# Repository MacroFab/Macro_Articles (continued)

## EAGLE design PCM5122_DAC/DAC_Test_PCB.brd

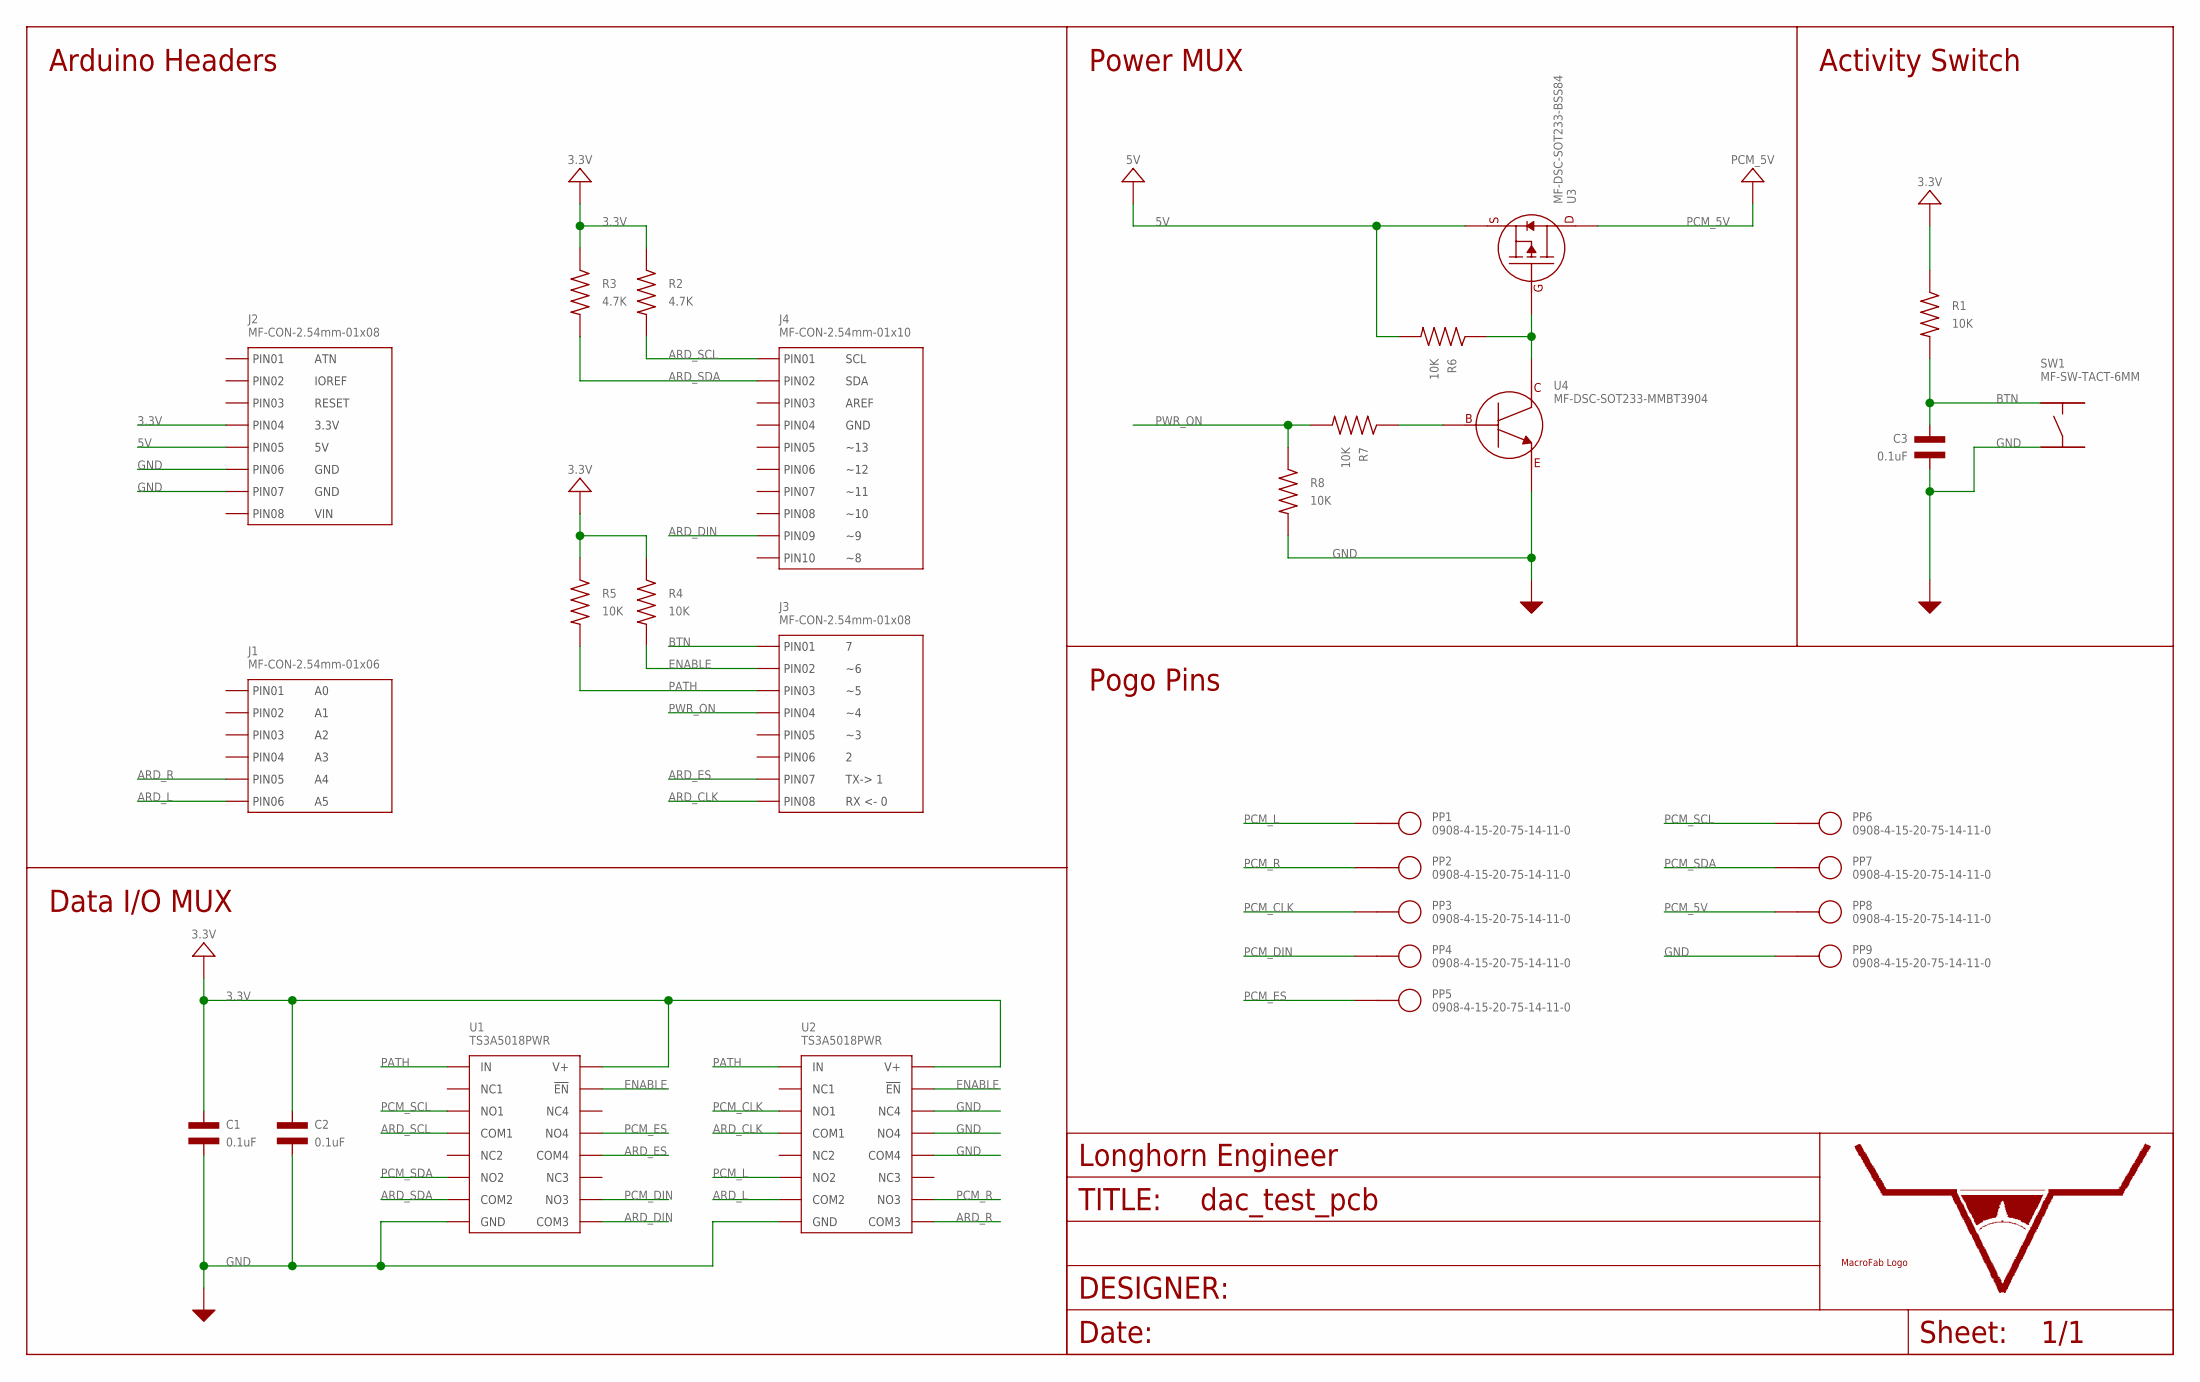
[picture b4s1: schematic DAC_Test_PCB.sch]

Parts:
C1, C2, C3: 0.1uF; C0603
J1: MF-CON-2.54mm-01x06; PTH_2.54MM_01X06
J2, J3: MF-CON-2.54mm-01x08; PTH_2.54MM_01X08
J4: MF-CON-2.54mm-01x10; PTH_2.54MM_01X10
PP1, PP2, PP3, PP4, PP5, PP6, PP7, PP8, PP9: 0908-4-15-20-75-14-11-0
R1, R4, R5, R6, R7, R8: 10K; R0603
R2, R3: 4.7K; R0603
SW1: MF-SW-TACT-6MM; TACT6MM
U1, U2: TS3A5018PWR; TS3A5018_TTSOP-16
U3: MF-DSC-SOT233-BSS84; SOT-23-3
U4: MF-DSC-SOT233-MMBT3904; SOT-23-3
U$8: LHE_FRAME
U$9: MF_LOGOLOGO_MEDIUM; MF_LOGO_MEDIUM

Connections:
3.3V: C1.P$1, C2.P$1, J2.P$4 (PIN4), R1.P$1, R2.P$1, R3.P$1, R4.P$1, R5.P$1, U1.16 (V+), U2.16 (V+)
5V: J2.P$5 (PIN5), R6.P$2, U3.P$2 (SOURCE)
ARD_CLK: J3.P$8 (PIN8), U2.4 (COM1)
ARD_DIN: J4.P$9 (PIN9), U1.9 (COM3)
ARD_ES: J3.P$7 (PIN7), U1.12 (COM4)
ARD_L: J1.P$6 (PIN6), U2.7 (COM2)
ARD_R: J1.P$5 (PIN5), U2.9 (COM3)
ARD_SCL: J4.P$1 (PIN1), R2.P$2, U1.4 (COM1)
ARD_SDA: J4.P$2 (PIN2), R3.P$2, U1.7 (COM2)
BASE: R7.P$1, U4.P$1 (BASE)
BTN: C3.P$1, J3.P$1 (PIN1), R1.P$2, SW1.P$1
COLLECTOR: R6.P$1, U3.P$1 (GATE), U4.P$3 (COLLECTOR)
ENABLE: J3.P$2 (PIN2), R4.P$2, U1.15 (EN'), U2.15 (EN')
GND: C1.P$2, C2.P$2, C3.P$2, J2.P$6 (PIN6), J2.P$7 (PIN7), PP9.P$1, R8.P$2, SW1.P$3, U1.8 (GND), U2.8 (GND), U2.12 (COM4), U2.13 (NO4), U2.14 (NC4), U4.P$2 (EMITTER)
PATH: J3.P$3 (PIN3), R5.P$2, U1.1 (IN), U2.1 (IN)
PCM_5V: PP8.P$1, U3.P$3 (DRAIN)
PCM_CLK: PP3.P$1, U2.3 (NO1)
PCM_DIN: PP4.P$1, U1.10 (NO3)
PCM_ES: PP5.P$1, U1.13 (NO4)
PCM_L: PP1.P$1, U2.6 (NO2)
PCM_R: PP2.P$1, U2.10 (NO3)
PCM_SCL: PP6.P$1, U1.3 (NO1)
PCM_SDA: PP7.P$1, U1.6 (NO2)
PWR_ON: J3.P$4 (PIN4), R7.P$2, R8.P$1

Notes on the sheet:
Arduino Headers
Data I/O MUX
Power MUX
Activity Switch
Pogo Pins

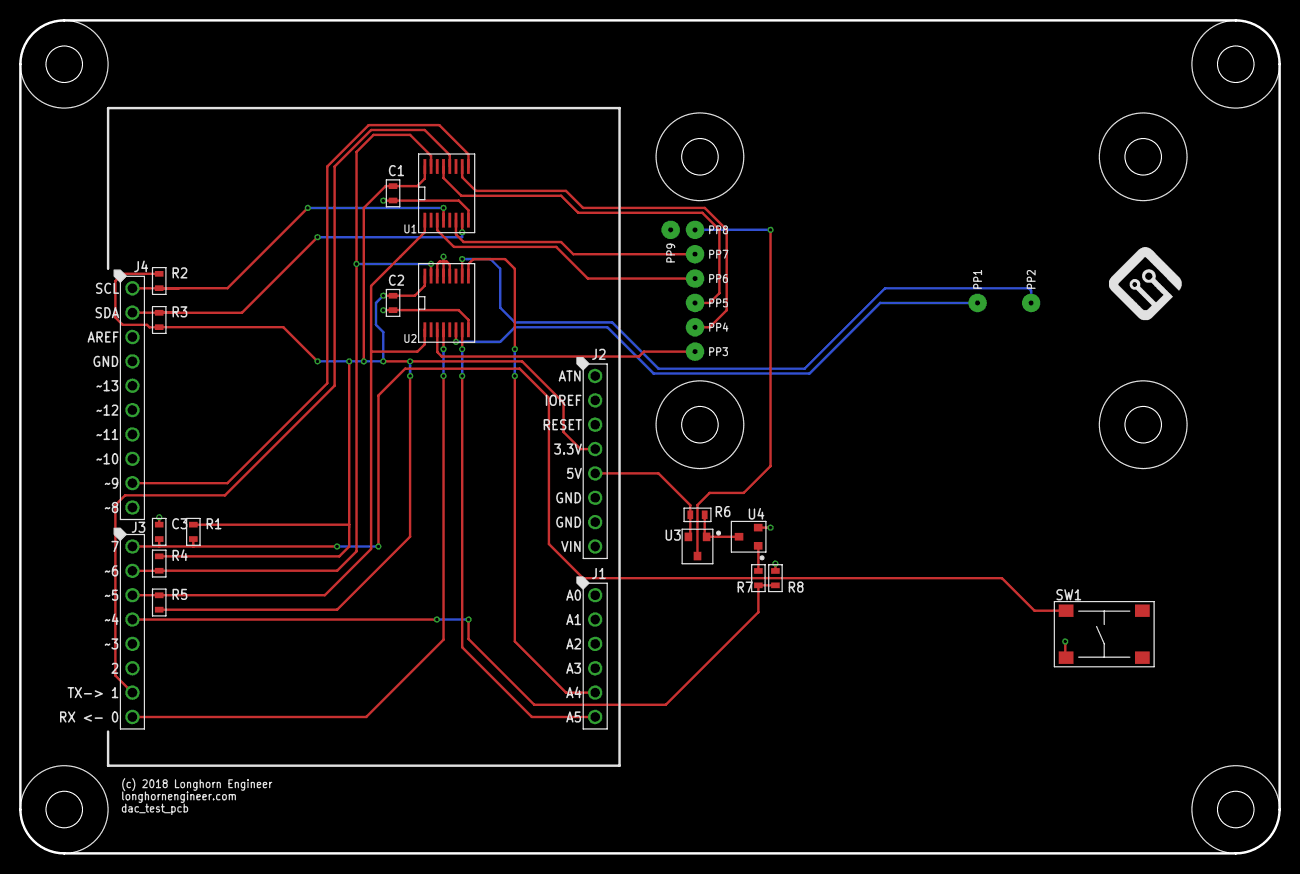
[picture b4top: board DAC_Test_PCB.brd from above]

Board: 2 copper layers, 131.3 x 86.9 mm, 39 parts (0 on the bottom side), 24 nets.

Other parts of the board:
U$4, U$5, U$6, U$7, U$16, U$17, U$18, U$19: MOUNT_HOLE_150MIL

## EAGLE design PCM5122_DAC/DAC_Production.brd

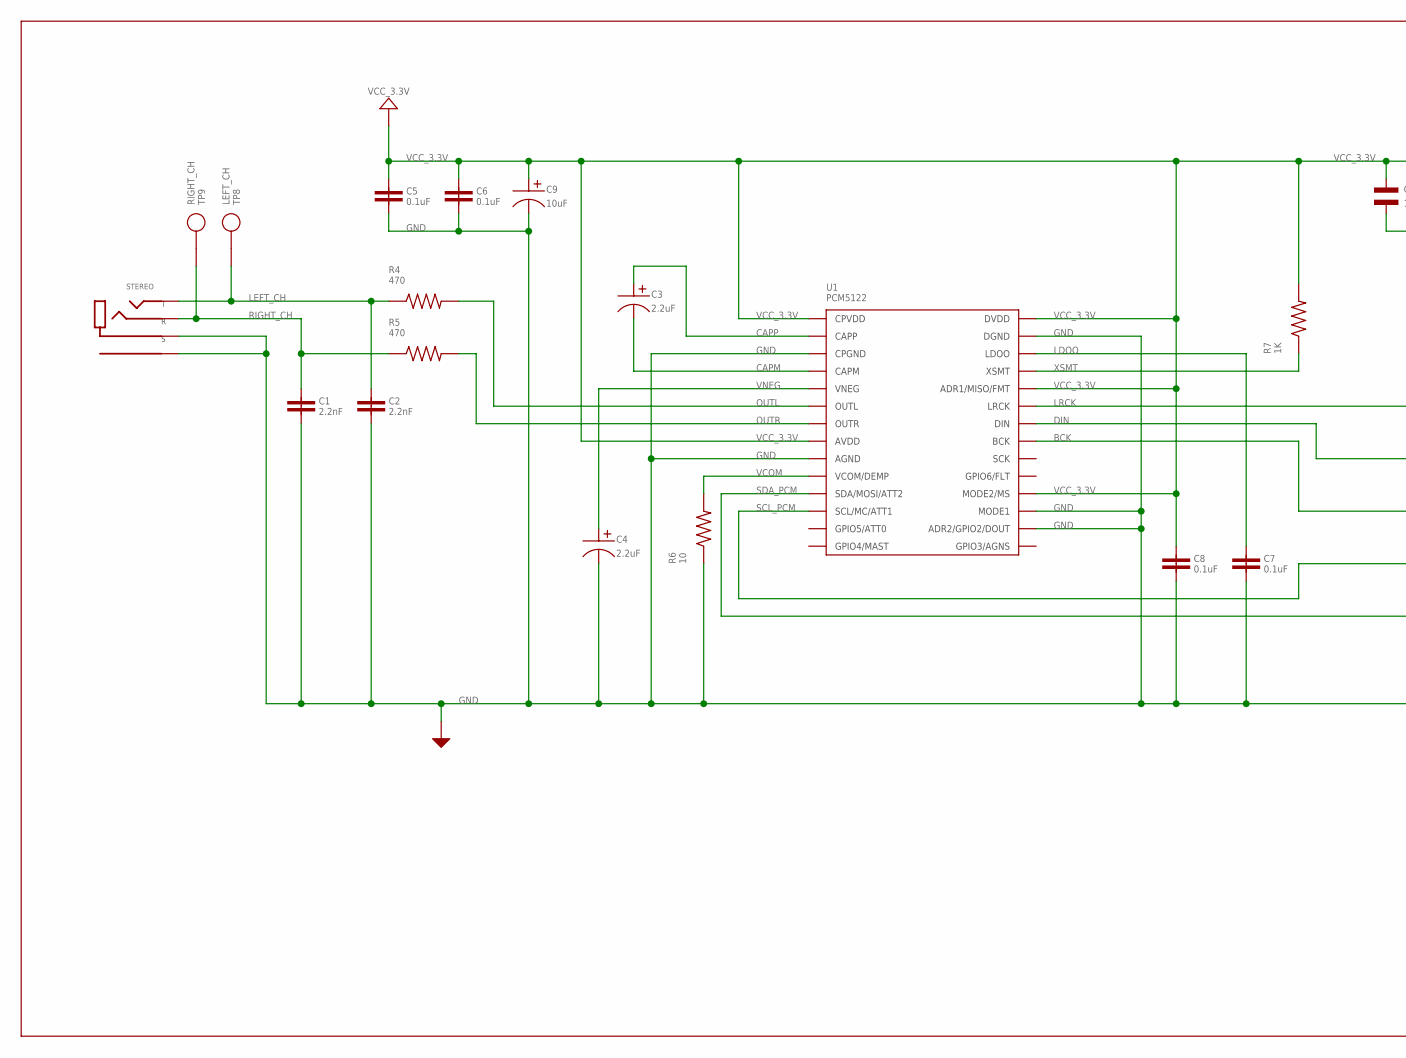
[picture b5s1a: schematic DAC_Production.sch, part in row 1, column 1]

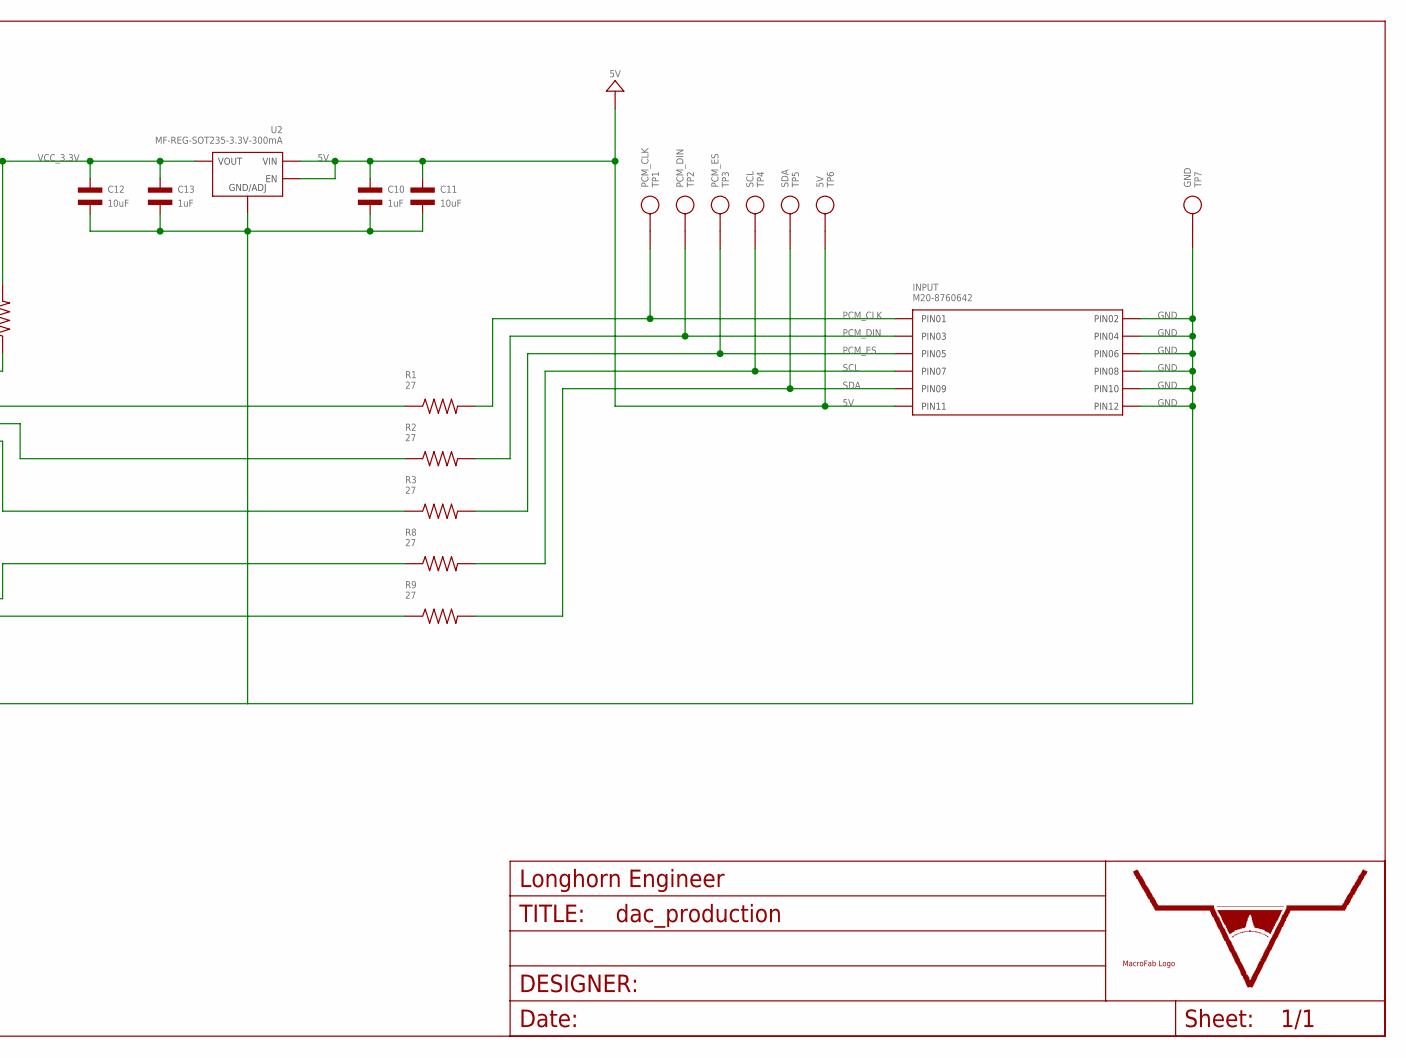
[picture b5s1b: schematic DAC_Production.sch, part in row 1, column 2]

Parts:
C1, C2: 2.2nF; 0805; MPN VJ0805A222KXXPW1BC
C3, C4: 2.2uF; CP4MM; MPN UUQ1H2R2MCL1GB
C5, C6, C7, C8: 0.1uF; 0805; MPN 885012207072
C9: 10uF; CP4MM; MPN UUQ1A100MCL1GB
C10, C13: 1uF; C0805; MPN MF-CAP-0805-1uF
C11, C12: 10uF; C1206; MPN MF-CAP-1206-10uF
INPUT: M20-8760642
R1, R2, R3, R8, R9: 27; 0603; MPN MF-RES-0603-27
R4, R5: 470; 0603; MPN MF-RES-0603-470
R6: 10; 0603; MPN MF-RES-0603-10
R7: 1K; 0603; MPN MF-RES-0603-1K
STEREO: TRS_SHIELD_JACK_SJ1-3533NS; SJ1-3533NS
TP1: PCM_CLK; ROUND_TP
TP2: PCM_DIN; ROUND_TP
TP3: PCM_ES; ROUND_TP
TP4: SCL; ROUND_TP
TP5: SDA; ROUND_TP
TP6: 5V; ROUND_TP
TP7: GND; ROUND_TP
TP8: LEFT_CH; ROUND_TP
TP9: RIGHT_CH; ROUND_TP
U1: PCM5122; PCM5122_TTSOP-28
U2: MF-REG-SOT235-3.3V-300mA; SOT-23-5
U$8: LHE_FRAME
U$9: MF_LOGOLOGO_MEDIUM; MF_LOGO_MEDIUM

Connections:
5V: C10.P$1, C11.P$1, INPUT.P$11 (PIN11), TP6.P$1, U2.P$1 (VIN), U2.P$3 (EN)
BCK: R3.1, U1.P$21 (BCK)
CAPM: C3.P$2, U1.P$4 (CAPM)
CAPP: C3.P$1, U1.P$2 (CAPP)
DIN: R2.1, U1.P$22 (DIN)
GND: C1.2, C2.2, C4.P$2, C5.2, C6.2, C7.2, C8.2, C9.P$2, C10.P$2, C11.P$2, C12.P$2, C13.P$2, INPUT.P$2 (PIN2), INPUT.P$4 (PIN4), INPUT.P$6 (PIN6), INPUT.P$8 (PIN8), INPUT.P$10 (PIN10), INPUT.P$12 (PIN12), R6.1, STEREO.1_A (S), STEREO.1_B (S), STEREO.S1 (SHIELD), STEREO.S2 (SHIELD), STEREO.S3 (SHIELD), STEREO.S4 (SHIELD), STEREO.S5 (SHIELD), STEREO.S6 (SHIELD), TP7.P$1, U1.P$3 (CPGND), U1.P$9 (AGND), U1.P$16 (ADR2/GPIO2/DOUT), U1.P$17 (MODE1), U1.P$27 (DGND), U2.P$2 (GND/ADJ)
LDOO: C7.1, U1.P$26 (LDOO)
LEFT_CH: C2.1, R4.1, STEREO.2_A (T), STEREO.2_B (T), TP8.P$1
LRCK: R1.1, U1.P$23 (LRCK)
OUTL: R4.2, U1.P$6 (OUTL)
OUTR: R5.2, U1.P$7 (OUTR)
PCM_CLK: INPUT.P$1 (PIN1), R1.2, TP1.P$1
PCM_DIN: INPUT.P$3 (PIN3), R2.2, TP2.P$1
PCM_ES: INPUT.P$5 (PIN5), R3.2, TP3.P$1
RIGHT_CH: C1.1, R5.1, STEREO.3_A (R), STEREO.3_B (R), TP9.P$1
SCL: INPUT.P$7 (PIN7), R8.2, TP4.P$1
SCL_PCM: R8.1, U1.P$12 (SCL/MC/ATT1)
SDA: INPUT.P$9 (PIN9), R9.2, TP5.P$1
SDA_PCM: R9.1, U1.P$11 (SDA/MOSI/ATT2)
VCC_3.3V: C5.1, C6.1, C8.1, C9.P$1, C12.P$1, C13.P$1, R7.2, U1.P$1 (CPVDD), U1.P$8 (AVDD), U1.P$18 (MODE2/MS), U1.P$24 (ADR1/MISO/FMT), U1.P$28 (DVDD), U2.P$5 (VOUT)
VCOM: R6.2, U1.P$10 (VCOM/DEMP)
VNEG: C4.P$1, U1.P$5 (VNEG)
XSMT: R7.1, U1.P$25 (XSMT)

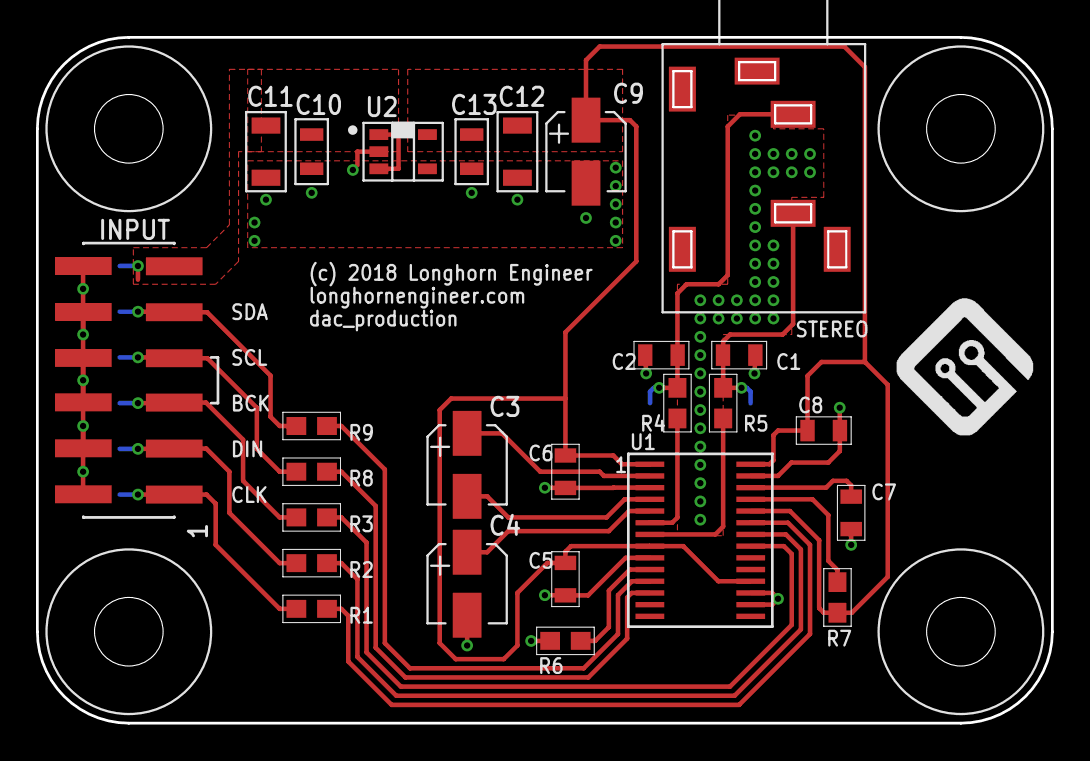
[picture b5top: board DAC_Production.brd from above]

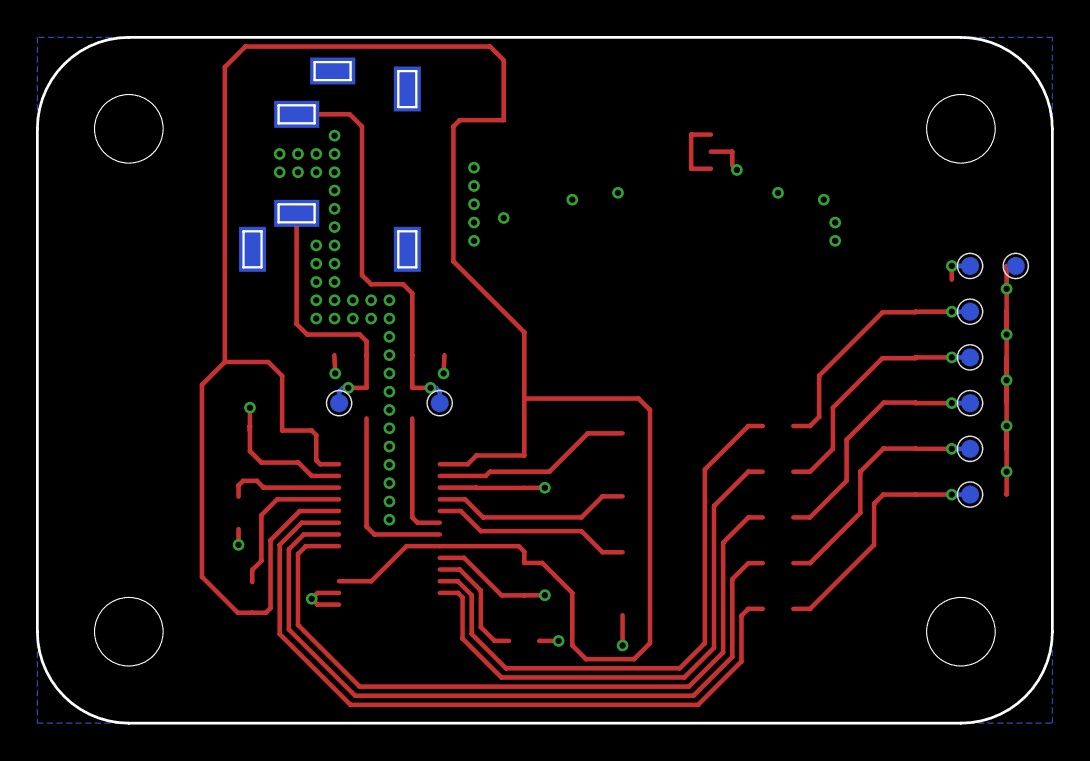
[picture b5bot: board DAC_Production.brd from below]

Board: 2 copper layers, 56.4 x 38.1 mm, 41 parts (9 on the bottom side), 23 nets.

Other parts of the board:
U$4, U$5, U$6, U$7: MOUNT_HOLE_150MIL

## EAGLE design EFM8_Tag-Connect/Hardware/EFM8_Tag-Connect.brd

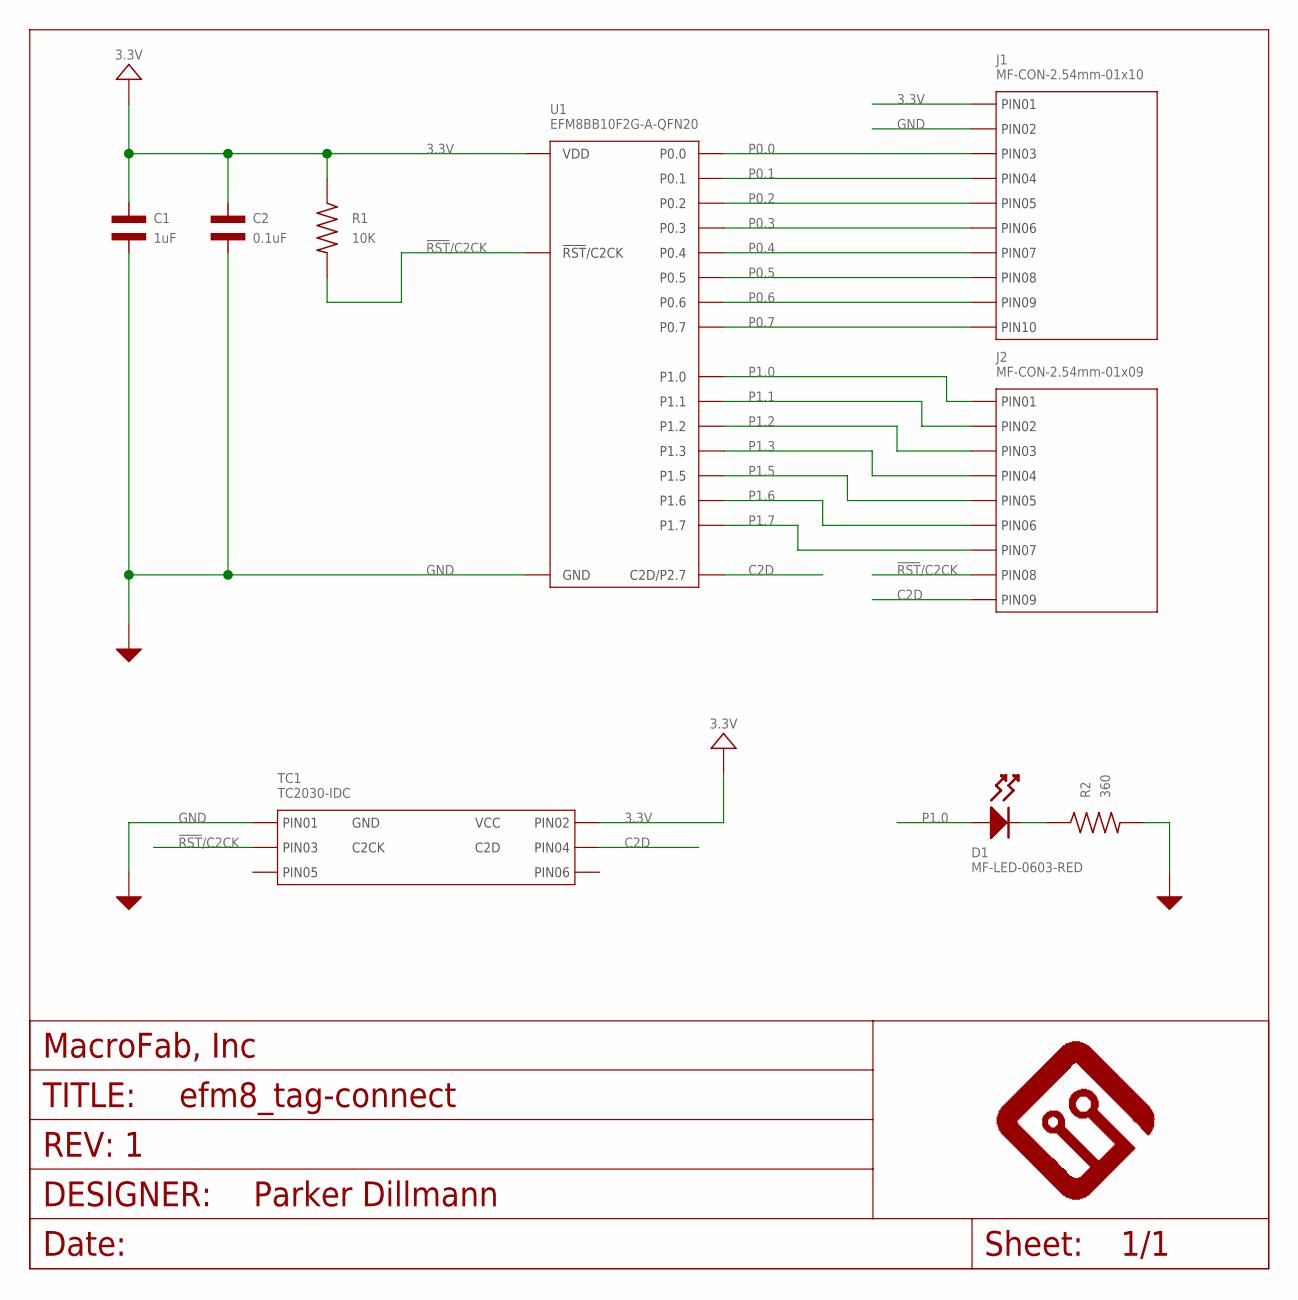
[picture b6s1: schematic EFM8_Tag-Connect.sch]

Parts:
C1: 1uF; C0402; MPN MF-CAP-0402-1uF
C2: 0.1uF; C0402; MPN MF-CAP-0402-0.1uF
D1: MF-LED-0603-RED; LED0603
FRAME1: MF_FRAMEDEFAULT; MF_FRAME_DEFAULT
J1: MF-CON-2.54mm-01x10; PTH_2.54MM_01X10
J2: MF-CON-2.54mm-01x09; PTH_2.54MM_01X09
R1: 10K; R0402; MPN MF-RES-0402-10K
R2: 360; R0402; MPN MF-RES-0402-360
TC1: TC2030-IDC; TC2030-IDC-FP
U1: EFM8BB10F2G-A-QFN20; EFM8BB10F(2/4/8)G-A-QFN20; MPN EFM8BB10F2G-A-QFN20

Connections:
3.3V: C1.P$1, C2.P$1, J1.P$1 (PIN1), R1.P$1, TC1.P$2 (PIN2), U1.P$4 (VDD)
!RST!/C2CK: J2.P$8 (PIN8), R1.P$2, TC1.P$3 (PIN3), U1.P$5 (!RST!/C2CK)
C2D: J2.P$9 (PIN9), TC1.P$4 (PIN4), U1.P$6 (C2D/P2.7)
GND: C1.P$2, C2.P$2, J1.P$2 (PIN2), R2.P$2, TC1.P$1 (PIN1), U1.P$3 (GND), U1.P$12 (GND), U1.PAD (GND)
unnamed: D1.CATHODE, R2.P$1
P0.0: J1.P$3 (PIN3), U1.P$2 (P0.0)
P0.1: J1.P$4 (PIN4), U1.P$1 (P0.1)
P0.2: J1.P$5 (PIN5), U1.P$20 (P0.2)
P0.3: J1.P$6 (PIN6), U1.P$19 (P0.3)
P0.4: J1.P$7 (PIN7), U1.P$18 (P0.4)
P0.5: J1.P$8 (PIN8), U1.P$17 (P0.5)
P0.6: J1.P$9 (PIN9), U1.P$16 (P0.6)
P0.7: J1.P$10 (PIN10), U1.P$15 (P0.7)
P1.0: D1.ANODE, J2.P$1 (PIN1), U1.P$14 (P1.0)
P1.1: J2.P$2 (PIN2), U1.P$13 (P1.1)
P1.2: J2.P$3 (PIN3), U1.P$11 (P1.2)
P1.3: J2.P$4 (PIN4), U1.P$10 (P1.3)
P1.5: J2.P$5 (PIN5), U1.P$8 (P1.5)
P1.6: J2.P$6 (PIN6), U1.P$7 (P1.6)
P1.7: J2.P$7 (PIN7), U1.P$9 (P1.7)

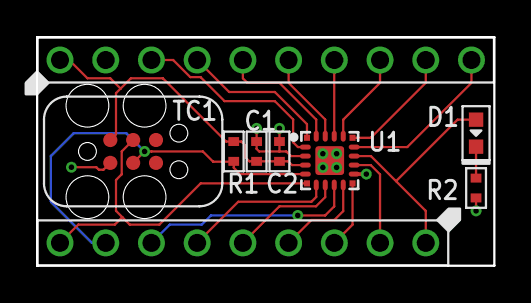
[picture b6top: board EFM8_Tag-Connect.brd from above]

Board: 2 copper layers, 25.4 x 12.7 mm, 10 parts (1 on the bottom side), 20 nets.

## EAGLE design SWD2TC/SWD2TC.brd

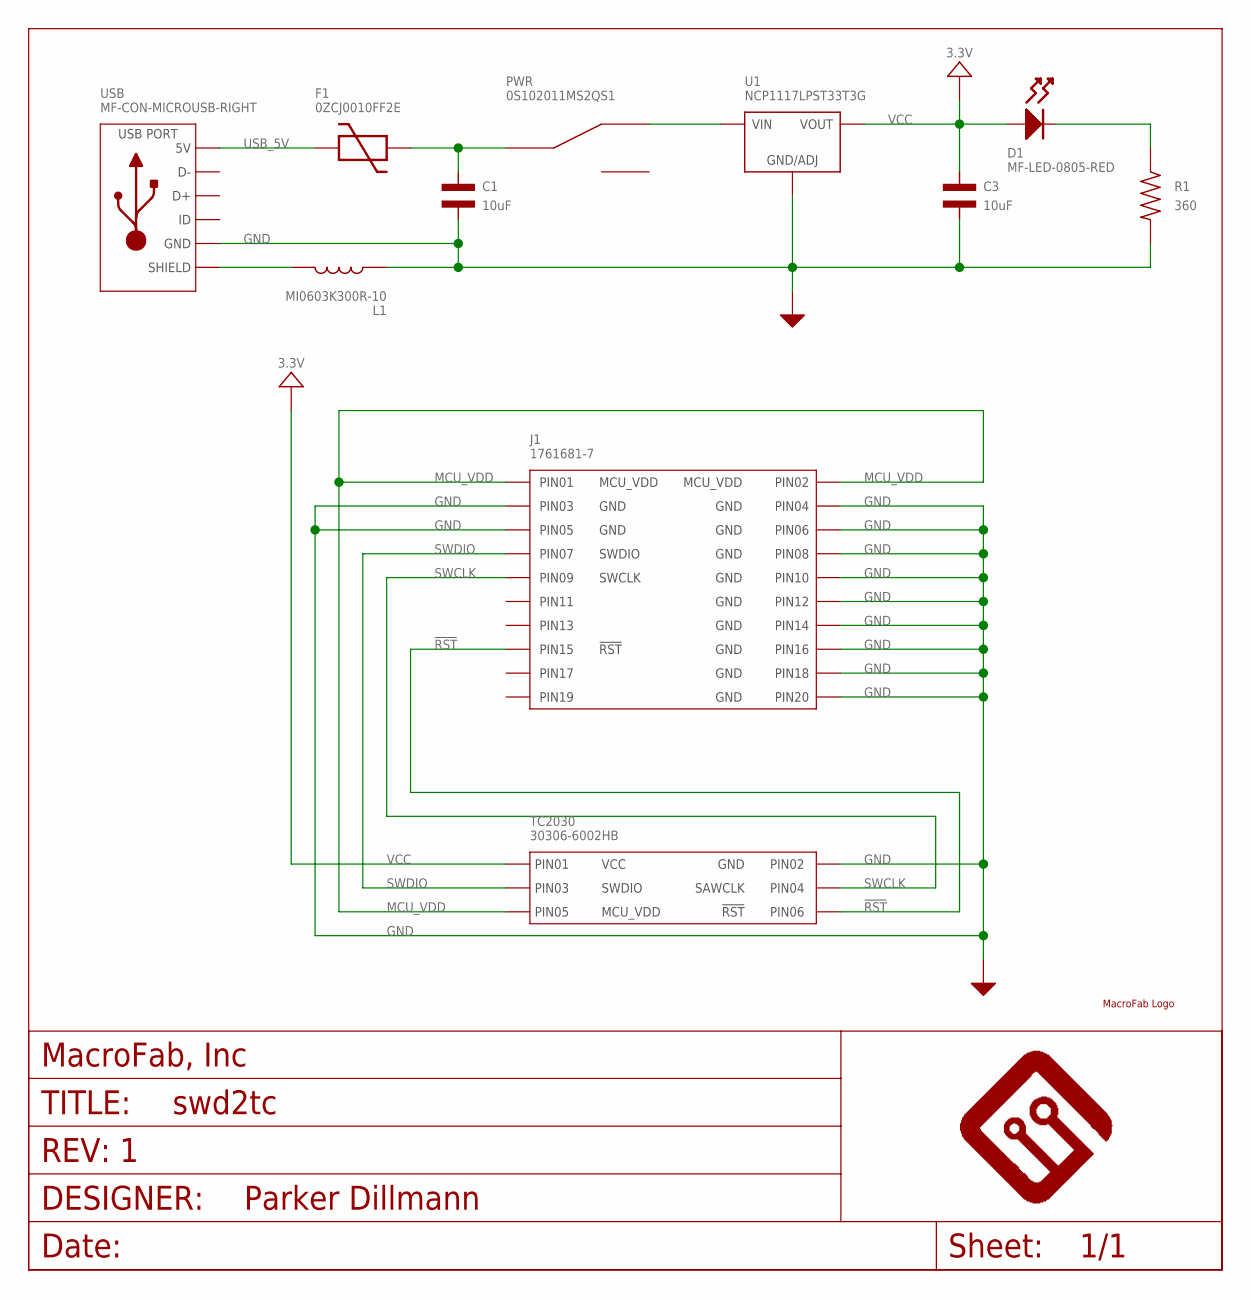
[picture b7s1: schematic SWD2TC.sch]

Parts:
C1, C3: 10uF; C1206; MPN MF-CAP-1206-10uF
D1: MF-LED-0805-RED; LED0805
F1: 0ZCJ0010FF2E; 1206; MPN 0ZCJ0010FF2E
FRAME1: MF_FRAMEDEFAULT; MF_FRAME_DEFAULT
J1: 1761681-7
L1: MI0603K300R-10; L0603; MPN MI0603K300R-10
PWR: 0S102011MS2QS1; MPN 0S102011MS2QS1
R1: 360; R0805; MPN MF-RES-0805-360
TC2030: 30306-6002HB
U1: NCP1117LPST33T3G; SOT-223-3
U$3: MF_LOGOLOGO_MEDIUM; MF_LOGO_MEDIUM
USB: MF-CON-MICROUSB-RIGHT; MICROUSB-RIGHT

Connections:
!RST: J1.P$15 (15), TC2030.6 (PIN6)
GND: C1.P$2, C3.P$2, J1.P$3 (3), J1.P$4 (4), J1.P$5 (5), J1.P$6 (6), J1.P$8 (8), J1.P$10 (10), J1.P$12 (12), J1.P$14 (14), J1.P$16 (16), J1.P$18 (18), J1.P$20 (20), L1.P$1, R1.P$2, TC2030.2 (PIN2), U1.P$2 (GND/ADJ), USB.5 (GND)
MCU_VDD: J1.P$1 (1), J1.P$2 (2), TC2030.5 (PIN5)
unnamed: D1.CATHODE, R1.P$1
unnamed: C1.P$1, F1.2, PWR.2 (C)
unnamed: L1.P$2, USB.S1 (SLD), USB.S2 (SLD), USB.S3 (SLD), USB.S4 (SLD), USB.S5 (SLD), USB.S6 (SLD)
unnamed: PWR.1, U1.P$4 (VIN)
SWCLK: J1.P$9 (9), TC2030.4 (PIN4)
SWDIO: J1.P$7 (7), TC2030.3 (PIN3)
USB_5V: F1.1, USB.1 (5V)
VCC: C3.P$1, D1.ANODE, TC2030.1 (PIN1), U1.P$1 (VOUT), U1.P$3 (VOUT)

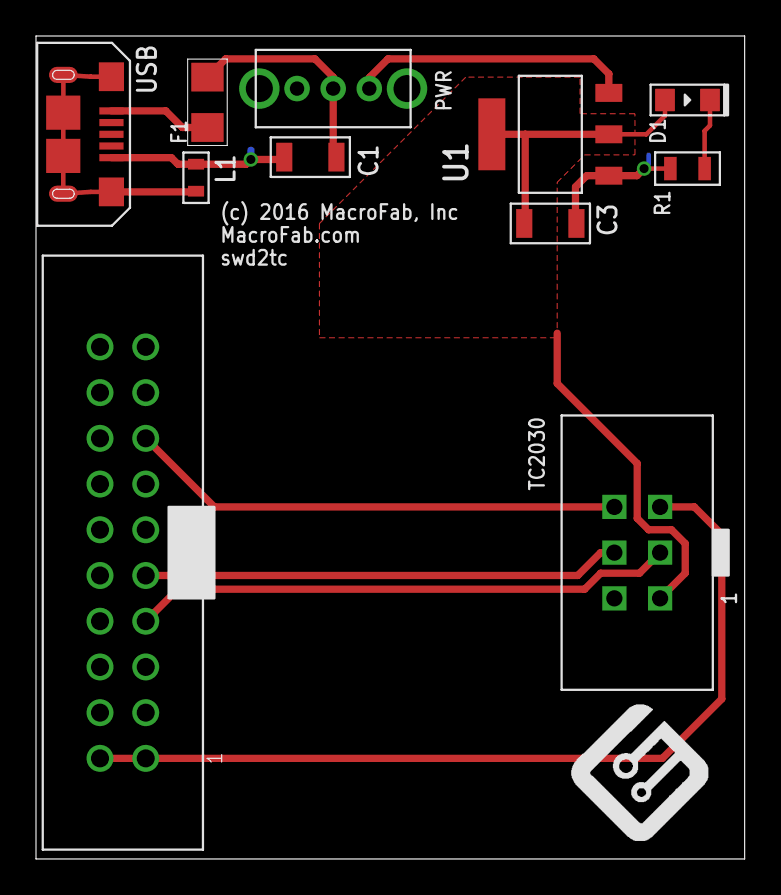
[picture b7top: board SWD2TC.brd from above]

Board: 2 copper layers, 39.4 x 45.7 mm, 13 parts (0 on the bottom side), 11 nets.
